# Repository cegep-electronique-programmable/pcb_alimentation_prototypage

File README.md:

# Carte d'alimentation de prototypage

Cette carte génére une tension de 3.3V ou 5V et se branche sur une plaquette de prototypage(breadboard).

La plage de tension d'entrée recommandée est 9V à 37V.

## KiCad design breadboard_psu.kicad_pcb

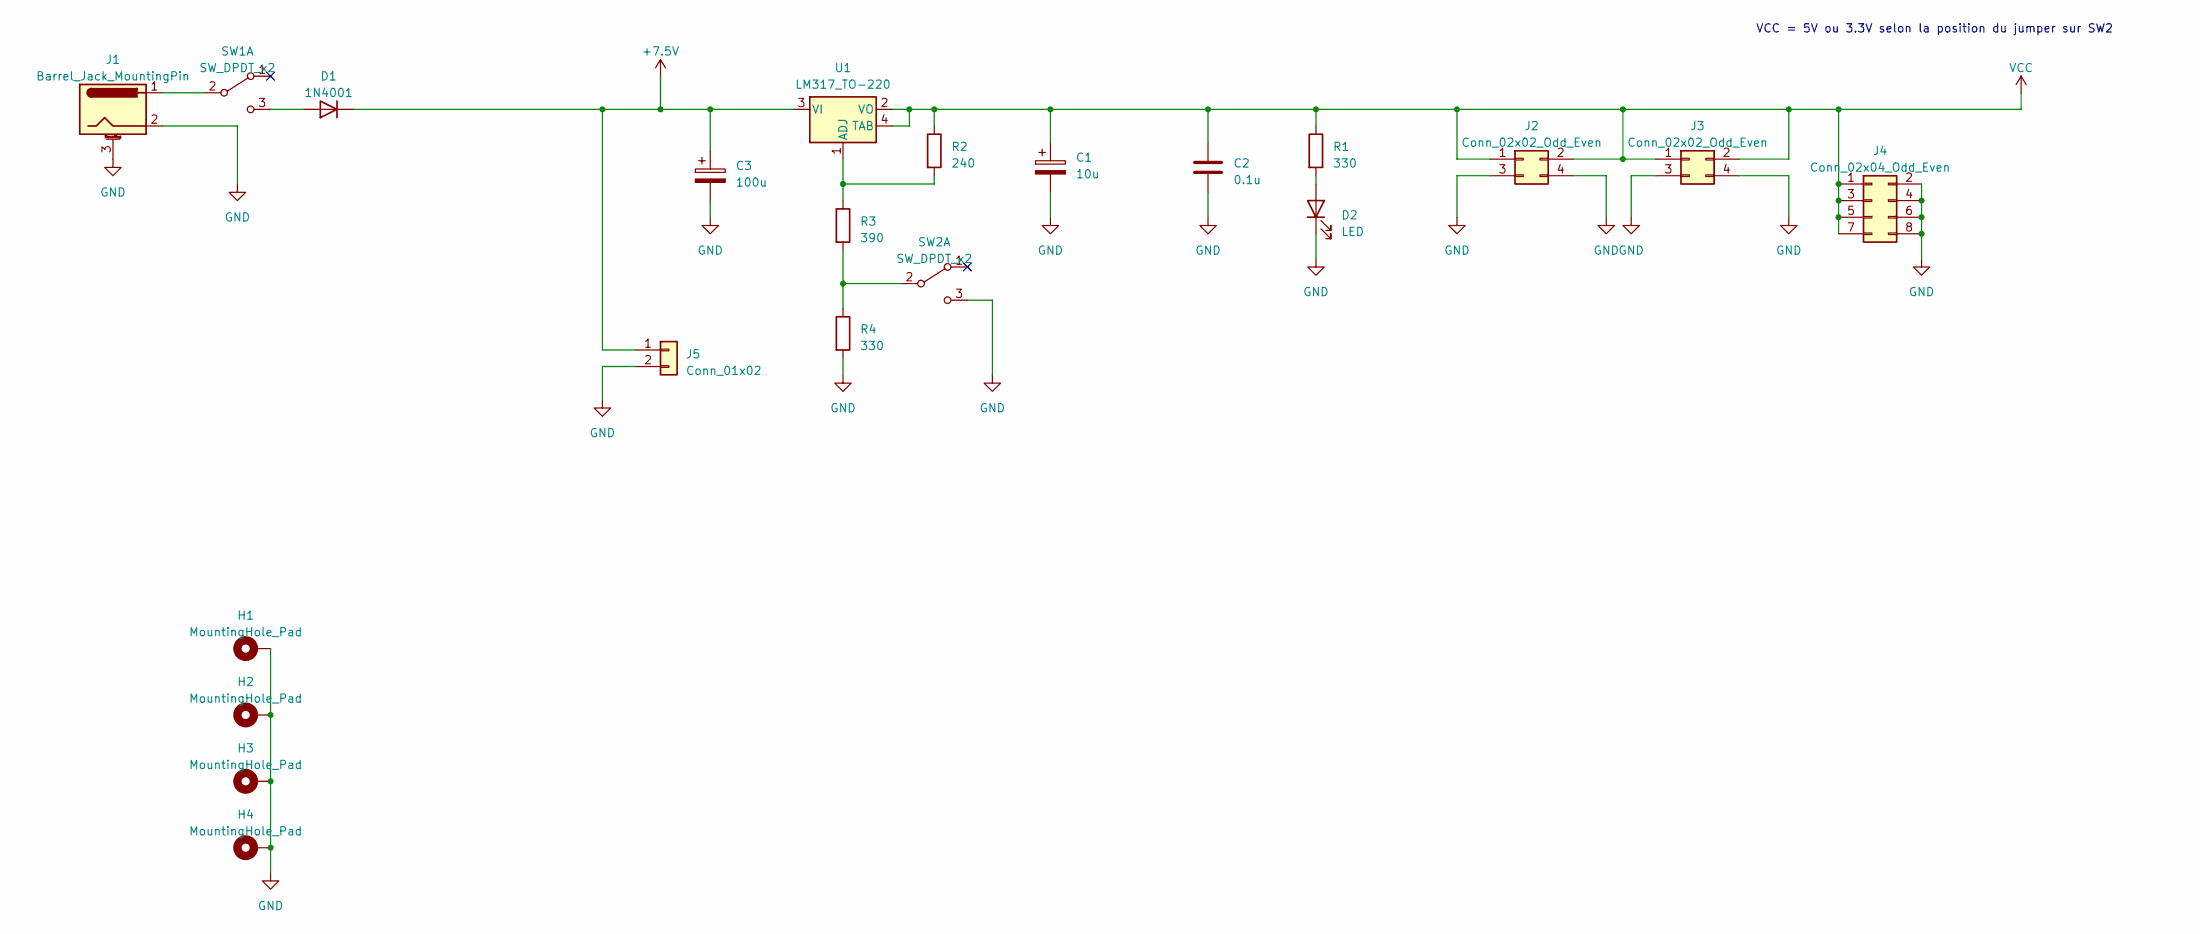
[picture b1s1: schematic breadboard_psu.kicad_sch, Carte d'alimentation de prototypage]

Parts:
C1: 10u; CP_Radial_D5.0mm_P5.0mm_EEU-EB1J100SB; MPN EEU-EB1J100SB
C2: 0.1u; C_Rect_L4.0mm_W2.5mm_P5.00mm_RDER71H104K0K1H03B; MPN RDER71H104K0K1H03B
C3: 100u; CP_Radial_D6.3mm_P2.50mm_Oversized; MPN ES5107M016AE1EA
D1: 1N4001; D_DO-41_SOD81_P7.62mm_Horizontal_Oversized; MPN 1N4001RLG
D2: LED; LED_D5.0mm_Oversized; MPN XLUG12D
H1, H2, H3, H4: MountingHole_Pad; MountingHole_2.5mm_Pad_TopBottom
J1: Barrel_Jack_MountingPin; BarrelJack_Horizontal_PJ-002A_Oversized; MPN PJ-002A
J2, J3: Conn_02x02_Odd_Even; PinHeader_2x02_P2.54mm_Vertical_Oversized
J4: Conn_02x04_Odd_Even; PinHeader_2x04_P2.54mm_Vertical_Oversized
J5: Conn_01x02; PinSocket_1x02_P2.54mm_Vertical_Oversized
R1, R4: 330; R_Axial_DIN0207_L6.3mm_D2.5mm_P7.62mm_Horizontal_Oversized
R2: 240; R_Axial_DIN0207_L6.3mm_D2.5mm_P7.62mm_Horizontal_Oversized
R3: 390; R_Axial_DIN0207_L6.3mm_D2.5mm_P7.62mm_Horizontal_Oversized
SW1, SW2: SW_DPDT_x2; PinHeader_1x03_P2.54mm_Vertical_Oversized
U1: LM317_TO-220; TO-220-3_Horizontal_TabDown_Connected_Oversized; MPN LM317KCS

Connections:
+7.5V: C3.1, D1.1 (K), J5.1, U1.3 (VI)
GND: C1.2, C2.2, C3.2, D2.1 (K), H1.1, H2.1, H3.1, H4.1, J1.2, J1.3 (MountPin), J2.3, J2.4, J3.3, J3.4, J4.2, J4.4, J4.6, J4.8, J5.2, R4.2, SW2.3 (C)
unnamed: D1.2 (A), SW1.3 (C)
unnamed: D2.2 (A), R1.2
unnamed: J1.1, SW1.2 (B)
unnamed: R3.2, R4.1, SW2.2 (B)
unnamed: R2.2, R3.1, U1.1 (ADJ)
VCC: C1.1, C2.1, J2.1, J2.2, J3.1, J3.2, J4.1, J4.3, J4.5, J4.7, R1.1, R2.1, U1.2 (VO), U1.4 (TAB)

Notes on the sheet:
VCC = 5V ou 3.3V selon la position du jumper sur SW2

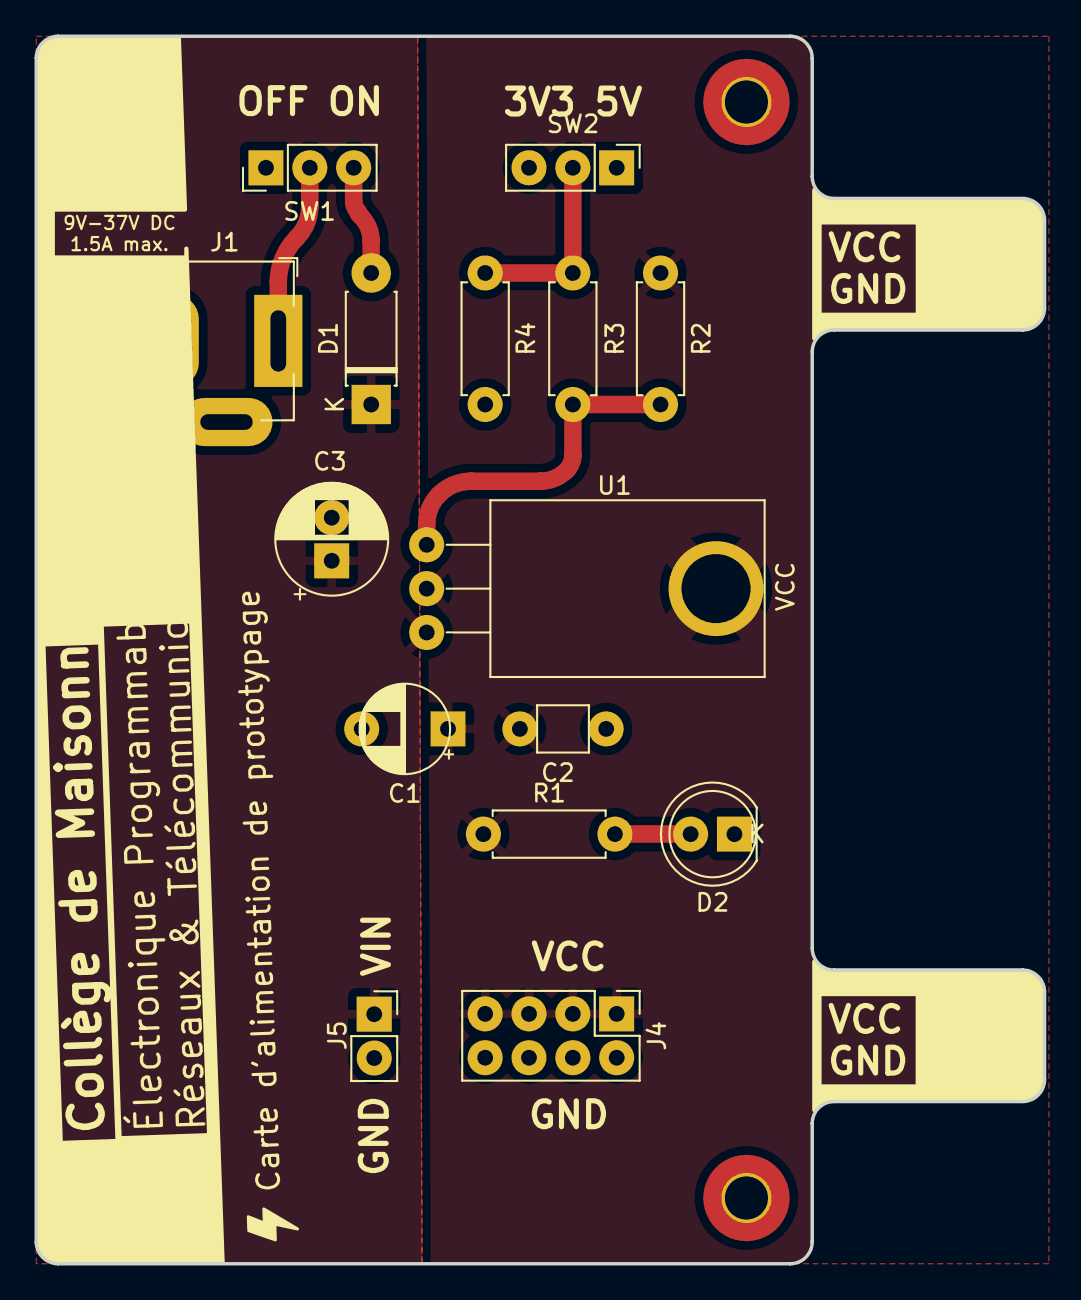
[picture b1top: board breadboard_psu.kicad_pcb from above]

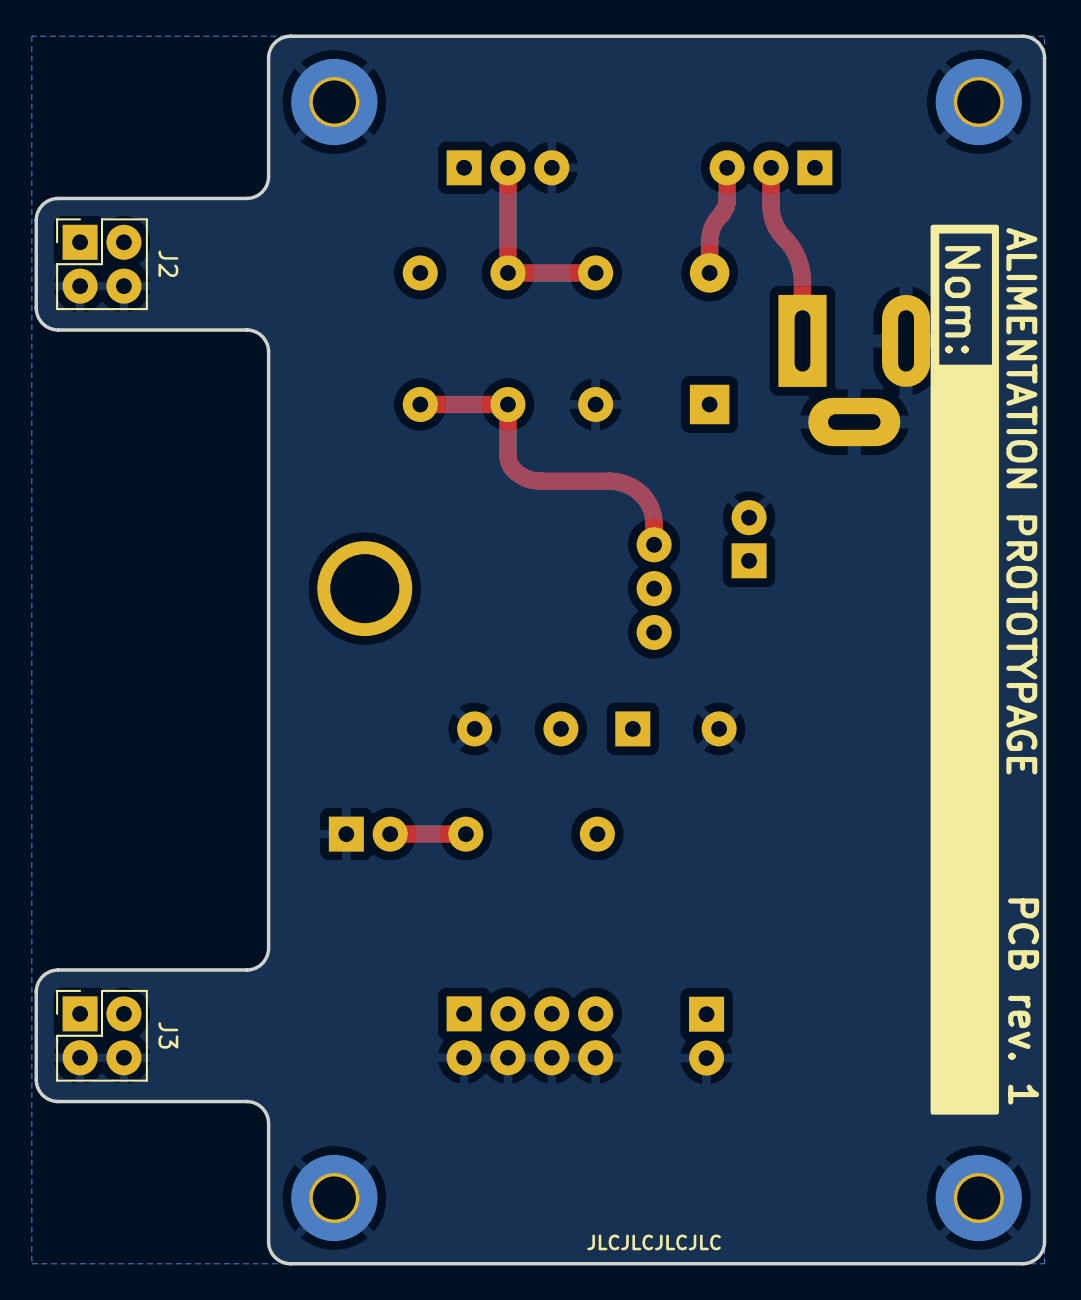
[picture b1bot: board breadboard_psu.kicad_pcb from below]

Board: 2 copper layers, 58.4 x 71.1 mm, 21 parts (2 on the bottom side), 8 nets.

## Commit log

2023-05-16 Alonger les tabs
2023-05-16 MaJ TO220 a plat + esthétique
2023-05-16 Cartouche et mise en page
2023-05-16 Ajout MPN + BOM
2023-05-16 DEL 5mm
2023-05-16 4 pin par tab
2023-05-16 Trous a 36 mils
2023-05-16 Sauvegarde projet
2023-05-18 Largeur des tab fixé. Nouveau contour de carte
2023-05-18 Info des composants a jour
    MPN SPN footprint 3D
2023-05-18 Changement du silkscreen + Resistance & diode 300mils
2023-05-18 Finalisation silkscreen
2023-05-18 Cleanup
2023-05-18 Export doc + gerber
2023-05-18 Meilleure rendu
2023-05-18 Typo
2023-05-19 Trous et Beignes oversized
2023-05-19 Fichiers inutiles
2023-05-19 Footprint oversized
2023-05-19 Ajout BOM
2023-05-19 Maj Fichiers de production
2023-05-19 Maj Visuel
2023-05-19 Trous a 26 mils
2023-05-24 Ajout JLCJLCJLCJLC silkscreen bottom
2023-06-04 LED plus bas sur le PCB
